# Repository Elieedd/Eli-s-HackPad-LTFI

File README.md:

# Eli-s-HackPad-LTFI
I made a macropad under HackClub for drawing! I want to allow for more keybinds on my drawing tablet, hence the macropad! Also will be used for rythm games probably.

HACKAPAD LTFI

Schematic

PCB

CASE

It will fit together with 4 screws.
BOM
1x Seeed Studio Xiao RP2040
4x Cherry MX Switches
4x M3x5x4 Heatset Inserts
4x M3x16mm screws
4x white blank DSA keycaps
^Everything above is from the Hackpad Kit
1x Case (2 3 printed parts) (Unknown Price, buying from legion)
1x Soldering Kit $18
1x PCB $4.00
^Shipping for PCB $42.25 & Customs duties & taxes $1.40
Total $65.65

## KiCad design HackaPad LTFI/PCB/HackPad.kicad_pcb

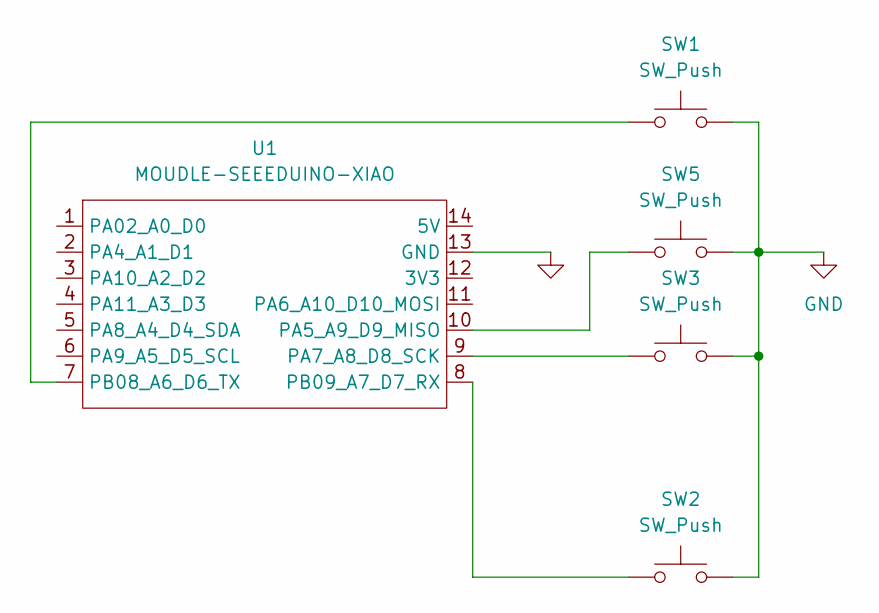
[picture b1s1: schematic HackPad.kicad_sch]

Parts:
SW1, SW2, SW3, SW5: SW_Push; SW_Cherry_MX_1.00u_PCB
U1: MOUDLE-SEEEDUINO-XIAO; XIAO-Generic-Hybrid-14P-2.54-21X17.8MM

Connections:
GND: SW1.2, SW2.2, SW3.2, SW5.2, U1.13 (GND)
unnamed: SW5.1, U1.10 (PA5_A9_D9_MISO)
unnamed: SW3.1, U1.9 (PA7_A8_D8_SCK)
unnamed: SW1.1, U1.7 (PB08_A6_D6_TX)
unnamed: SW2.1, U1.8 (PB09_A7_D7_RX)

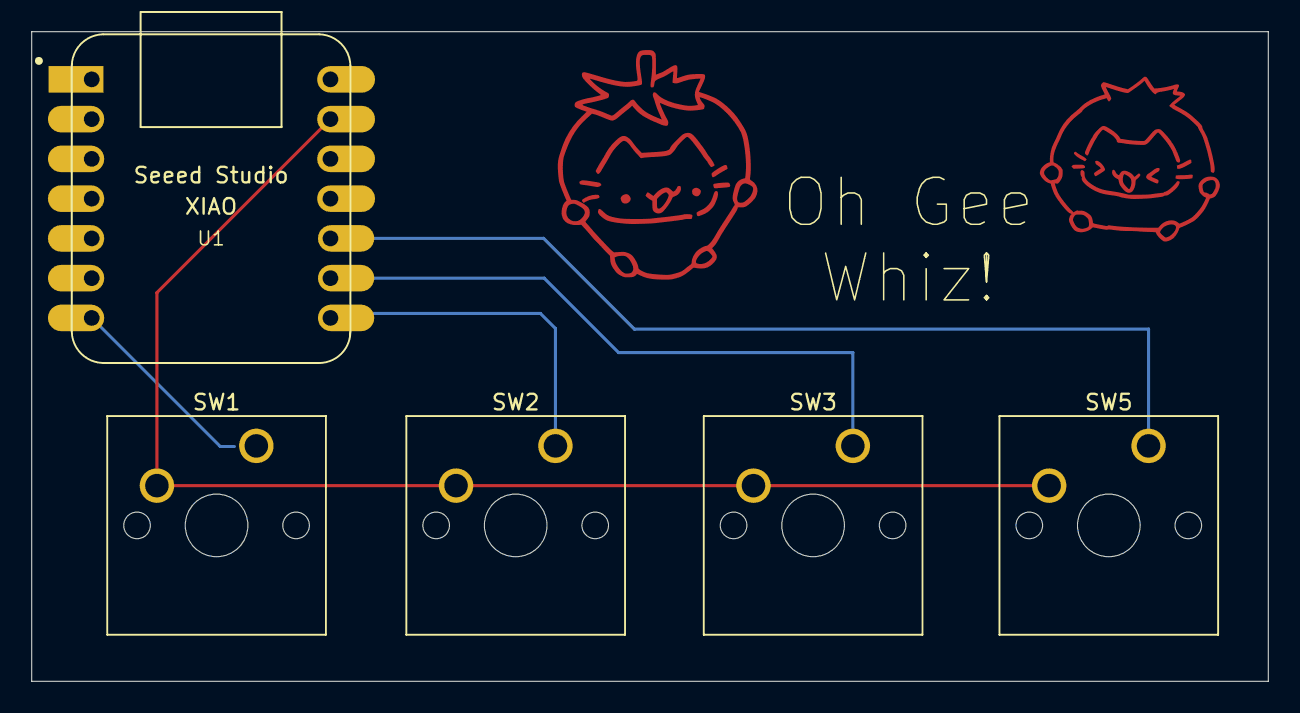
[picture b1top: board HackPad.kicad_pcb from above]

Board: 2 copper layers, 79.0 x 41.5 mm, 5 parts (0 on the bottom side), 5 nets.
